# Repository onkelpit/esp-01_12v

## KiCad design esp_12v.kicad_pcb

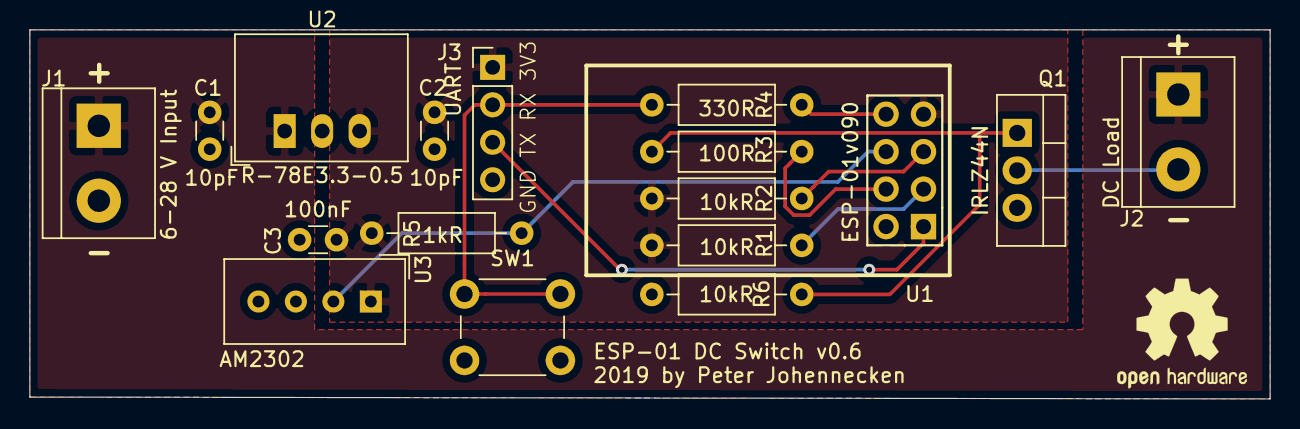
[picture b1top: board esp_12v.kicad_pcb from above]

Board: 2 copper layers, 84.1 x 25.0 mm, 17 parts (0 on the bottom side), 12 nets.

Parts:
C1, C2: 10pF; C_Disc_D3.0mm_W1.6mm_P2.50mm
C3: 100nF; C_Disc_D3.0mm_W1.6mm_P2.50mm
J1: 6-28 V Input; TerminalBlock_bornier-2_P5.08mm
J2: DC Load; TerminalBlock_bornier-2_P5.08mm
J3: UART; PinHeader_1x04_P2.54mm_Vertical
Q1: IRLZ44N; TO-220-3_Vertical
R1, R2, R6: 10kR; R_Axial_DIN0207_L6.3mm_D2.5mm_P10.16mm_Horizontal
R3: 100R; R_Axial_DIN0207_L6.3mm_D2.5mm_P10.16mm_Horizontal
R4: 330R; R_Axial_DIN0207_L6.3mm_D2.5mm_P10.16mm_Horizontal
R5: 1kR; R_Axial_DIN0207_L6.3mm_D2.5mm_P10.16mm_Horizontal
SW1: SW_Push; SW_PUSH_6mm
U1: ESP-01v090; ESP-01
U2: R-78E3.3-0.5; Converter_DCDC_RECOM_R-78E-0.5_THT
U3: AM2302; Aosong_DHT11_5.5x12.0_P2.54mm

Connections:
+3V3: C2.1, C3.1, J3.1, R1.2, R2.2, R5.1, U1.7, U2.3, U3.1
+12V: C1.1, J1.1, J2.1, U2.1
GND: C1.2, C2.2, C3.2, J1.2, J3.4, Q1.3, R6.2, SW1.2, U1.2, U2.2, U3.4
GPIO0: R5.2, U1.6, U3.2
GPIO2: R3.2, U1.4
unnamed: J2.2, Q1.2
unnamed: Q1.1, R3.1, R6.1
unnamed: R1.1, U1.3
unnamed: R2.1, U1.5
unnamed: R4.2, U1.8
RX: J3.2, R4.1, SW1.1
TX: J3.3, U1.1

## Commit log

2019-05-08 initial commit pcb version 0.5
2019-05-10 bumped to Version 0.6
    * changed dc jacks to terminalblocks
    * added decoupling cap for the thermal sensor
    * added 10kR between Gate and GND at the mosfet
